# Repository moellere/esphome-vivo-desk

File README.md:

# ESPHome VIVO Desk

An [ESPHome](https://esphome.io/) external component that integrates a **VIVO
electric standing desk** (DESK‑V110EW class, with a **DC‑KS7** handset) into Home
Assistant — reading the live **height** and driving **up / down / memory presets**
— while the **physical handset keeps working normally** (display, buttons,
sustained holds, presets).

It works as a transparent serial **interposer**: a small ESP board is spliced
into the two‑wire link between the desk's handset and its controller ("brain").
The component relays the handset⇄brain traffic in both directions (so the handset
stays fully functional), parses the height telemetry for Home Assistant, and can
inject up/down/preset commands from HA alongside the live relay.

> ⚠️ **Use at your own risk.** This involves cutting into your desk's handset
> cable and driving the controller over a reverse‑engineered serial protocol.
> It is not affiliated with or endorsed by VIVO. You are responsible for your
> own hardware.

## Hardware

- **An ESP board with two UARTs.** **ESP32 is strongly recommended** — its
  hardware UARTs are full‑duplex, which is required to relay the fast
  bidirectional traffic while a button is held. ESP8266 (software serial) can
  *read* height and fire one‑shot presets, but its half‑duplex serial cannot
  sustain a held‑button relay reliably. An ESP32‑C3 (e.g. SuperMini) works well.
- The desk's handset cable carries two data lines (handset→brain and
  brain→handset) plus power/ground. You splice the ESP in the middle.

### Wiring

The desk bus is **3.3 V / 5 V TTL UART, 19200 8N1**. Cut the two data wires and
route them through two UARTs on the ESP (pick any free GPIOs; example shown):

| Desk line            | ESP pin (example) | UART        |
|----------------------|-------------------|-------------|
| Handset TX (output)  | GPIO4 (RX)        | `hand_uart` |
| Handset RX (input)   | GPIO5 (TX)        | `hand_uart` |
| Brain TX (output)    | GPIO6 (RX)        | `brain_uart`|
| Brain RX (input)     | GPIO7 (TX)        | `brain_uart`|
| Desk GND             | GND (see note)    | —           |

Identify the two **TX** (output) wires by metering them to GND with the desk
powered and idle — a UART line rests **high**. The other wire in each pair is the
matching RX.

> 💡 **Grounding tip.** If you power the ESP from a *separate* supply (e.g. USB)
> than the desk, tie the desk GND to the ESP GND through a **~100 Ω series
> resistor**. A direct hard ground can form a ground loop that prevents boot,
> while no ground at all leaves the reference floating and the Wi‑Fi radio can
> brown out under load. The resistor gives a defined reference without a hard
> loop. (If you power the ESP *from* the desk's 5 V line, a single shared ground
> is cleanest and no resistor is needed.) **The ESP32‑C3 is not 5 V‑tolerant — if
> your desk's data lines are 5 V, level‑shift them.**

## Usage

```yaml
external_components:
  - source: github://moellere/esphome-vivo-desk
    components: [ vivo_desk ]

uart:
  - id: hand_uart
    rx_pin: GPIO4   # <- Handset TX
    tx_pin: GPIO5   # -> Handset RX
    baud_rate: 19200
  - id: brain_uart
    rx_pin: GPIO6   # <- Brain TX
    tx_pin: GPIO7   # -> Brain RX
    baud_rate: 19200

vivo_desk:
  id: desk
  hand_uart: hand_uart
  brain_uart: brain_uart
  height:
    name: "Desk Height"
```

See [`example.yaml`](example.yaml) for a complete device config including
switches for Up/Down and buttons for the M1–M4 presets, plus the diagnostic
toggles (relay / emulate / sniff) used while bringing a new desk online.

### From a YAML lambda

```yaml
- lambda: id(desk).start_up();     # hold up (until stop())
- lambda: id(desk).start_down();   # hold down
- lambda: id(desk).stop();         # stop movement
- lambda: id(desk).goto_preset(1); # recall stored preset 1..4
```

## Modes

- **Relay** (default): forwards handset⇄brain in both directions so the physical
  handset works (display + buttons + holds + presets), parses height for HA, and
  injects HA up/down/preset commands alongside.
- **Emulate**: the ESP *is* the handset toward the brain — height + control
  without a physical handset present. Streams the handset heartbeat/version/acks.
- **Silent**: pure listen (sniffer) — transmits nothing, logs both lines. Useful
  for capturing a new desk's protocol.

## Protocol

The handset⇄brain protocol (ASCII frames, `:cmd data checksum;`, 19200 8N1) is
documented in [`docs/PROTOCOL.md`](docs/PROTOCOL.md), including the height frame
format, command frames, the heartbeat, and the checksum.

## License

[MIT](LICENSE).

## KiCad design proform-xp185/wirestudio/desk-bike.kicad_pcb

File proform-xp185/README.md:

# ProForm XP 185 U under-desk bike (ESPHome)

Turns a ProForm XP 185 U (Sears 831.21741.0 / ICON PFCCEX01210) into an
under-desk bike controlled by an ESP32 running ESPHome, with a small
OLED + rotary encoder module as the local UI and everything exposed to Home
Assistant.

**The original console and handlebars are left intact.** The only thing the
build touches is the 8-pin harness coming up from the base: unplug it from the
console, plug it into the new controller. Put the harness back and the bike is
stock again.

The bike has no lower control board and no serial bus: the console *is* the
controller. It drives a 6 V gearmotor that moves the magnetic brake, reads that
motor's feedback potentiometer, counts a crank reed switch, and amplifies the
grip pulse pads. `desk-bike.yaml` reproduces the first three from an ESP32 and
takes heart rate from a BLE chest strap instead of the grips.

> ⚠️ Not affiliated with ICON / ProForm. Check everything with a meter before
> applying power; you are responsible for your own hardware.

## Bill of materials

| Part | Notes |
|---|---|
| ESP32 dev board (`esp32dev`) | Classic ESP32 or S3. An ESP32‑C3 Super Mini works with the alternate pin map in the YAML but is tight on pins and RAM with BLE + Wi‑Fi. |
| 1.3" OLED + EC11 encoder module (Estardyn, SH1116 driver, I2C) | The same module as the scroller project: SDA, SCL, VCC, GND, encoder A/B, PSH, CON (KEY1), BAK (KEY0). |
| H‑bridge | **Recommended:** two MOSFET half‑bridges from IRF4905 + IRFZ44N + 2N3904 (below). Alternatives: a DRV8833/TB6612 module, or a dual 5 V relay board. |
| 5 V supply | USB‑C receptacle with **5.1 kΩ from CC1 and CC2 to GND**, 2 A or better. 470 µF + 100 nF at the bridge's motor rail, 100 nF across the motor. |
| Mating connector for the harness | Whatever the console used (an 8‑pin JST‑XH‑style header on the console PCB), or splice a pigtail. |
| BLE heart‑rate strap (optional) | Anything exposing the standard Heart Rate Service. |
| Resistors | 2 × 10 kΩ (GPIO pull‑downs on the bridge inputs), 2 × 470 Ω, 2 × 1 kΩ, 2 × 5.1 kΩ (USB‑C CC). |

## Circuit

### 8‑pin harness from the base (measured on this bike)

| Pin | Function | Goes to |
|---|---|---|
| 1 | Motor A | bridge output A |
| 2 | Motor B | bridge output B |
| 3 | Pot supply | **3V3** (not 5 V, so the wiper stays inside the ADC range) |
| 4 | Pot wiper | `pin_pot` (GPIO34) |
| 5 | Pot ground | GND |
| 6 | Chassis ground | GND (common with 5 and 8 on the console PCB) |
| 7 | Reed switch | `pin_reed` (GPIO27); internal pull‑up enabled |
| 8 | Reed switch return | GND |

Pins 1/2 reverse polarity across the motor to move the magnets toward or away
from the flywheel. The console's own bridge used one 2N4401 + 2N4403 per
side, so the motor's stall current is under 600 mA.

### ESP32 pin map (defaults in the YAML `substitutions:`)

| Signal | ESP pin | Notes |
|---|---|---|
| Bridge IN1 | GPIO18 | 10 kΩ pull‑down to GND so the motor can't run during boot |
| Bridge IN2 | GPIO19 | 10 kΩ pull‑down to GND |
| Pot wiper | GPIO34 | ADC1, input‑only pin |
| Reed switch | GPIO27 | other side to GND |
| OLED SDA / SCL | GPIO21 / GPIO22 | 3V3 and GND to the module |
| Encoder A / B | GPIO16 / GPIO17 | internal pull‑ups |
| Encoder push (PSH) | GPIO25 | internal pull‑up |
| Back (BAK / KEY0) | GPIO26 | internal pull‑up |
| Confirm (CON / KEY1) | GPIO33 | internal pull‑up |

### Recommended bridge: two MOSFET half‑bridges

(Editable SVG: `wirestudio/hbridge-schematic.svg`.)

Three parts per half‑bridge, no heat, nearly the full 5 V at the motor, and
the FET body diodes handle flyback. Build two, one per motor pin.

| Part | Pin | Connects to |
|---|---|---|
| IRF4905 (P‑MOSFET) | source | +5 V rail |
| IRF4905 | drain | MOTOR pin (harness 1 or 2) |
| IRF4905 | gate | node D |
| IRFZ44N (N‑MOSFET) | source | GND |
| IRFZ44N | drain | MOTOR pin |
| IRFZ44N | gate | node D |
| R1 470 Ω | | node D to +5 V |
| Q1 2N3904 (or 2N2222 / BC337) | collector | node D |
| Q1 | emitter | GND |
| Q1 | base | R2 1 kΩ to ESP GPIO (IN1 or IN2) |
| R3 10 kΩ | | ESP GPIO to GND |

GPIO **high** → Q1 on → node D ≈ 0 V → P‑FET on, N‑FET off → motor pin at
5 V. GPIO **low** → Q1 off → node D pulled to 5 V → P‑FET off, N‑FET on →
motor pin at GND. A floating GPIO at boot reads low through R3, so both pins
start grounded. TO‑220 pinout, flat face toward you, legs down, left→right:
**G‑D‑S**, tab = drain. 2N3904 flat face toward you: **E‑B‑C**. IRF9540
substitutes for the IRF4905. Do not use the 600 V FQPF parts on the low
side; their 3–5 V threshold is too high for a 5 V gate.

| IN1 | IN2 | Pin 1 | Pin 2 | Motor |
|---|---|---|---|---|
| low | low | GND | GND | off (dynamic brake) |
| high | low | +5 V | GND | direction A |
| low | high | GND | +5 V | direction B |
| high | high | +5 V | +5 V | off |

No combination passes current through a leg. The YAML still passes through
all‑off for one 50 ms tick before reversing.

### Alternative: dual relay board

Two SPDT relays: relay 1 COM → motor pin 1, relay 2 COM → motor pin 2, both
NO → +5 V, both NC → GND, VCC/JD‑VCC → 5 V, IN1/IN2 → the bridge GPIOs. Most
boards are active‑low: set `bridge_active_low: "true"`. If a relay clicks in
during boot, add 10 kΩ from that IN pin to 5 V.

### Power and grounding

One 5 V supply feeds everything. The ESP takes its 3.3 V from its own
regulator; the pot is fed from that 3.3 V. Make a single star ground at the
bridge/ESP; the harness grounds (5, 6, 8) and the chassis all land there.
Bring the motor rail in through the 470 µF + 100 nF pair at the bridge.

### Layout (perfboard)

Left to right, matching signal flow:

1. **USB‑C receptacle** with the two 5.1 kΩ CC resistors, feeding a 5 V rail
   along the top edge and GND along the bottom.
2. **Bridge** next to the harness connector: the two TO‑220 pairs side by
   side, their 2N3904 drivers and 470 Ω / 1 kΩ / 10 kΩ in front of them, the
   470 µF across the rails right there.
3. **Harness header** (8‑pin) on the edge: 1/2 to the bridge outputs, 3 to
   3V3, 4 to GPIO34, 5/6/8 to GND, 7 to GPIO27.
4. **ESP32** in the middle, GPIO side facing the bridge.
5. **OLED/encoder module** on a 4‑pin + 5‑pin header (or a short ribbon) so it
   can mount on the desk edge; keep the I2C leads under ~30 cm.

### WireStudio design

`wirestudio/design.json` models the whole controller for
[wirestudio](https://github.com/moellere/WireStudio): board, I2C bus, OLED,
encoder, three keys, pot ADC, reed input, and the MOSFET bridge as an
`hbridge_mosfet` component. That component and the library subcircuit
support it relies on shipped in WireStudio 0.3x
([WireStudio#262](https://github.com/moellere/WireStudio/pull/262)). The same
design is saved on the studio at wirestudio.dorktool.com as `desk-bike`.

| File | What it is |
|---|---|
| `wiring.txt` | pin map, passives, power budget; validates with no warnings in strict mode |
| `bom.csv` | every part with designators: Q1/Q4 IRF4905, Q2/Q5 IRFZ44N, Q3/Q6 2N3904, R1–R6, C1, C2, J1 motor terminal, J2 USB-C with R7/R8 and C3 |
| `desk-bike.skidl.py` | run with SKiDL to get `desk-bike.kicad_sch` |
| `cpl.csv` | JLCPCB pick-and-place positions |
| `desk-bike.kicad_pcb` | placed and autorouted board (Freerouting through wirestudio: 179 segments, 7 vias, every pad bound to its net) |
| `desk-bike-fab.zip` | JLCPCB upload bundle from the routed board: Gerbers, drill, BOM, CPL |

```
wirestudio-generate proform-xp185/wirestudio/design.json --strict \
  --out-ascii proform-xp185/wirestudio/wiring.txt
```

The USB-C input and its CC resistors are the `psu` instance of the
`usb_c_power_in` library part (WireStudio 0.39.0,
[#298](https://github.com/moellere/WireStudio/pull/298)): J2, R7/R8 5.1k, C3
10 µF, VBUS on the 5 V rail. The 8-pin harness connector needs passthrough connector
pins and a `net` connection target
([WireStudio#300](https://github.com/moellere/WireStudio/issues/300)); until
then add it in KiCad. The YAML wirestudio renders is a skeleton;
`desk-bike.yaml` is the real firmware (control loop, display pages, ride
tracking).

## Breadboard build (830-point)

(Editable SVG: `wirestudio/breadboard-layout.svg`; the wire list is printed on
the drawing.)

The ESP32‑DevKitC V4's pin rows are 1.0 in apart, so on a single 830‑point
board only **one** free tie point exists per pin, along one header. The
layout puts the module in rows **i** and **a** with the 3V3‑side header on
row i, so row **j** serves 5V, GND, 3V3, GPIO34, 27, 25, 26 and 33. The six
signals on the other header (GPIO16, 17, 18, 19, 21, 22) are reached by
seating a jumper in hole **e** of that column *before* pressing the module
in; it runs under the board and exits at the centre channel.

- Rails: + = 5 V, − = GND on both edges, joined at column 63; 5 V in from the
  USB‑C breakout at column 1. C1 470 µF (col 24) and C3 100 nF (col 53)
  across the bottom rail. A 3V3 mini‑bus is column 22 (rows f–j).
- Bridge on the bottom block: Q1/Q2/Q3 in columns 25–35, Q4/Q5/Q6 in
  40–50, standing TO‑220s with G‑D‑S in adjacent columns of row b, GPIO
  nodes at columns 36 and 51.
- RJ45 breakout in row j, columns 54–61 (pins 1–8, T568B colours); C2
  100 nF between the two motor pins (g57–g58).
- OLED/encoder cable on a 9‑pin header in row j, columns 25–33.

## Printed enclosure

See [`enclosure/`](enclosure/README.md): a parametric base + lid around the Perma‑Proto snap‑in tray, with a keystone port for the Cat‑6 harness extension, a USB‑C slot and the OLED/encoder module in the lid.

## The local UI

| Control | Action |
|---|---|
| Encoder turn | resistance level 1–8 (also `number.desk_bike_resistance_level` in HA) |
| Encoder push, short | next display page |
| Encoder push, hold 1–3 s | reset ride time and distance |
| Back | drop to level 1 (coast) and remember the previous level |
| Confirm | return to the remembered level |

Pages: **Ride** (level, rpm, ride clock, distance, time of day, heart rate),
**Goals** (odometer, next milestone, progress bar), **Heart rate** (large, plus strap status), **Brake** (pot voltage, target,
moving/idle, fault — the calibration page).

## Calibration

The brake is positioned by **burst‑and‑settle**: the motor runs for a short
burst, stops, waits 100 ms, and only then is the pot read (8‑sample average,
no motor current flowing, so no ground bounce and no coasting error). The
loop then decides the next burst, shorter as it gets close, and stops when
the settled reading is within `deadband_v` of the target. A move that
doesn't advance the wiper for `max_stalled_bursts` bursts, or runs past
`stall_timeout_ms`, raises **Brake Motor Fault**.

Levels map to wiper voltages through the eight‑entry `level_volts` table.
Magnetic drag rises steeply as the gap closes, so the useful tension lives in
the last part of the travel; a linear spread puts most levels where you feel
almost nothing. Measure the two ends, then bunch the levels toward the heavy
end:

1. Flash with the defaults and open the **Brake** page (or Home Assistant).
2. Press **Brake Jog IN1** a few times and watch the voltage. If it *rises*,
   leave `in1_raises_pot: "true"`; if it falls, set `"false"`.
3. Jog to the lightest position you want as level 1 and note the voltage, v1.
4. Jog the other way until the motor stalls at the heavy end, back off a few
   hundredths of a volt, note the voltage, v8. Pedal: this is level 8.
5. Fill `level_volts` with eight values from v1 to v8. A good start is
   `v1 + (v8 - v1) * sqrt((i - 1) / 7)` for i = 1..8, which is what the
   default table is for v1 = 0.40, v8 = 2.90. Then ride a few minutes at each
   level and move individual entries until the steps feel even.
6. Re‑flash.

If a level change ends in **Brake Motor Fault**, the Brake page shows the
settled position, the target and the burst count: a target outside the
measured range, the wrong `in1_raises_pot`, or a jam are the usual causes.
Change the level again to clear it.

## Distance, odometer and milestones

Distance is what a bike with a **27.5 in tire** would cover: 2.194 m per wheel
turn. A tire size alone doesn't give distance per pedal stroke, so there is
also a virtual `gear_ratio` (wheel turns per crank turn). The default 2.1 is
about a 34T x 16T gear: 4.61 m per stroke, 12 mph at 70 rpm. Change either
substitution to taste; `use_miles` switches the OLED and milestone text.

- **Ride Distance / Ride Time / Speed** are per session (hold the encoder to
  reset).
- **Odometer** is lifetime distance. The crank count behind it is stored in
  flash (written at most every 5 minutes) so it survives reboots and OTA
  updates. It is `total_increasing` with `device_class: distance`, which is
  what Home Assistant's utility meter needs.
  `desk_bike_package.yaml` is a ready package with daily, weekly, monthly
  and yearly meters. Copy it into `<config>/packages/` keeping an underscore
  name: HA uses the filename as the package slug and rejects hyphens.
- **Milestones** unlock on lifetime distance: Length of Manhattan, English
  Channel, Pontchartrain Causeway, a marathon, Panama Canal, Hadrian's Wall
  (117.5 km), a century ride, Katy Trail, Grand Canyon, Across Arkansas
  (I-40, 458 km), Natchez Trace, Pacific Coast Highway, Land's End to John
  o'Groats, a Tour de France, Appalachian Trail, Route 66, New York to LA,
  the Ming Great Wall, and around the Earth. The list is one table in the
  YAML; keep it sorted if you add your own.
  Each unlock publishes **Last Milestone**, shows a 15 s banner on the OLED,
  and fires the HA event `esphome.desk_bike_milestone` (`title`,
  `odometer_km`) for automations. **Next Milestone** and **Milestone
  Progress** show what's coming; the OLED's *Goals* page has the same with a
  progress bar.

## Heart rate

Set `hrm_mac`. On boot with the strap on, the ESPHome log lists nearby BLE
devices with their MACs. The **Heart rate** page shows whether the strap is
connected. (The grip electrodes on the handlebars are not used; they need
both hands on the bars, which doesn't fit desk use. An AD8232 version lives
in this repo's history if you ever want it.)

## Entities

| Entity | Type | Purpose |
|---|---|---|
| Resistance Level | number 1–8 | Sets the brake |
| Cadence, Crank Revolutions | sensor | From the reed switch |
| Ride Time, Ride Distance, Speed | sensor | Session counters; Reset Ride button clears them |
| Odometer | sensor | Lifetime distance, kept in flash; source for HA utility meters |
| Last Milestone, Next Milestone, Milestone Progress | text / sensor | Distance achievements |
| Pedaling | binary | Cadence > 0 |
| Heart Rate | sensor | From the BLE strap |
| Button, Back, Confirm | binary | The module's keys, for your own automations |
| Brake Position, Brake Moving, Brake Motor Fault | diagnostics | Loop state |
| Brake Jog IN1 / IN2 / Stop | buttons | Calibration and manual override |

## Config layout

`desk-bike.yaml` follows the same shape as the scroller project: `common/
base.yaml` and `common/sensor.yaml` are merged in, fonts come from
`common/fonts/` (slkscr, BebasNeue‑Regular, arial). Remember that a
`base.yaml` brings wifi/api/ota/logger in through `packages:`, which
deep‑merge, so the `wifi:` block here only adds `fast_connect` and
`power_save_mode: none`. Keys merged with `<<:` do not deep‑merge, so this
file's `sensor:` list replaces `sensor.yaml`'s; uptime and Wi‑Fi signal are
repeated in it.

## Not included (yet)

- **Bluetooth FTMS** so Zwift or similar can read cadence and set resistance.
  ESPHome's `esp32_ble_server` can host the service, but the ESP would then be
  a BLE central (strap) and peripheral (FTMS) at once, so budget memory.
- A power estimate. The console's watts were a lookup of level × cadence; do
  the same in a template sensor once you have numbers you trust.

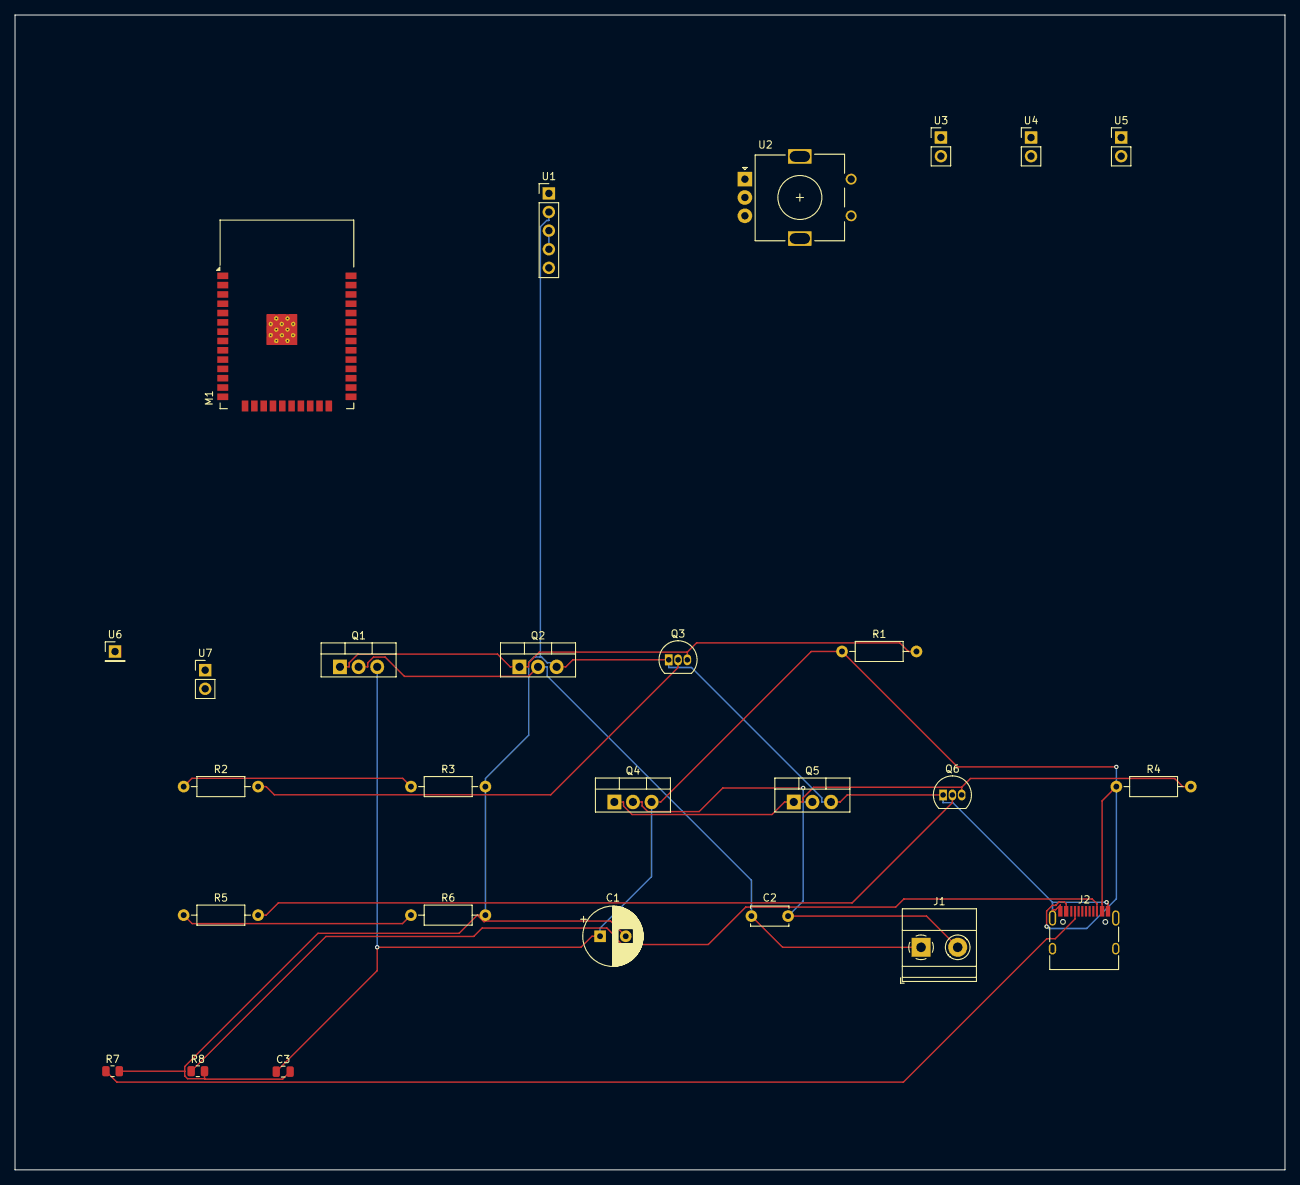
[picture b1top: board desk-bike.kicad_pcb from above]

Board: 2 copper layers, 173.3 x 157.6 mm, 27 parts (0 on the bottom side), 13 nets.

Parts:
C1: 470uF; CP_Radial_D8.0mm_P3.50mm
C2: 100nF; C_Disc_D5.0mm_W2.5mm_P5.00mm
C3: 10uF; C_0805_2012Metric
J1: Motor; TerminalBlock_Phoenix_MKDS-1,5-2_1x02_P5.00mm_Horizontal
J2: USB-C; USB_C_Receptacle_HRO_TYPE-C-31-M-12
M1: esp32-devkitc-v4; ESP32-WROOM-32
Q1, Q4: IRF4905; TO-220-3_Vertical
Q2, Q5: IRFZ44N; TO-220-3_Vertical
Q3, Q6: 2N3904; TO-92_Inline
R1, R4: 470; R_Axial_DIN0207_L6.3mm_D2.5mm_P10.16mm_Horizontal
R2, R5: 1k; R_Axial_DIN0207_L6.3mm_D2.5mm_P10.16mm_Horizontal
R3, R6: 10k; R_Axial_DIN0207_L6.3mm_D2.5mm_P10.16mm_Horizontal
R7, R8: 5.1k; R_0805_2012Metric
U1: SSD1306; PinHeader_1x05_P2.54mm_Vertical
U2: Rotary encoder; RotaryEncoder_Alps_EC11E_Vertical_H20mm
U3, U4, U5: Input; PinHeader_1x02_P2.54mm_Vertical
U6: ADC sense; PinHeader_1x01_P2.54mm_Vertical
U7: Pulse source; PinHeader_1x02_P2.54mm_Vertical

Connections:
+5V: C1.1, C3.1, J2.A4, J2.A9, J2.B4, J2.B9, Q1.3, Q4.3, R1.1, R4.1
BUS_i2c0: U1.3, U1.4
GND: C1.2, C3.2, J2.A1, J2.A12, J2.B1, J2.B12, J2.S1, Q2.3, Q3.1, Q5.3, Q6.1, R3.2, R6.2, R7.2, R8.2, U1.2
GPIO_GPIO18: R2.1, R3.1
GPIO_GPIO19: R5.1, R6.1
bridge_base_a: Q3.2, R2.2
bridge_base_b: Q6.2, R5.2
bridge_gate_a: Q1.1, Q2.1, Q3.3, R1.2
bridge_gate_b: Q4.1, Q5.1, Q6.3, R4.2
bridge_out_a: C2.1, J1.1, Q1.2, Q2.2
bridge_out_b: C2.2, J1.2, Q4.2, Q5.2
psu_cc1: J2.A5, R7.1
psu_cc2: J2.B5, R8.1

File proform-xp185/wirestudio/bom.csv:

Comment,Designator,Footprint,JLCPCB Part #
100nF,C2,Capacitor_THT:C_Disc_D5.0mm_W2.5mm_P5.00mm,
10k,"R3,R6",Resistor_THT:R_Axial_DIN0207_L6.3mm_D2.5mm_P10.16mm_Horizontal,
10uF,C3,Capacitor_SMD:C_0805_2012Metric,
1k,"R2,R5",Resistor_THT:R_Axial_DIN0207_L6.3mm_D2.5mm_P10.16mm_Horizontal,
2N3904,"Q3,Q6",Package_TO_SOT_THT:TO-92_Inline,
470,"R1,R4",Resistor_THT:R_Axial_DIN0207_L6.3mm_D2.5mm_P10.16mm_Horizontal,
470uF,C1,Capacitor_THT:CP_Radial_D8.0mm_P3.50mm,
5.1k,"R7,R8",Resistor_SMD:R_0805_2012Metric,
ADC sense,U6,Connector_PinHeader_2.54mm:PinHeader_1x01_P2.54mm_Vertical,
ESP32-DevKitC-V4,M1,RF_Module:ESP32-WROOM-32,
IRF4905,"Q1,Q4",Package_TO_SOT_THT:TO-220-3_Vertical,
IRFZ44N,"Q2,Q5",Package_TO_SOT_THT:TO-220-3_Vertical,
Input,"U3,U4,U5",Connector_PinHeader_2.54mm:PinHeader_1x02_P2.54mm_Vertical,
Motor,J1,"TerminalBlock_Phoenix:TerminalBlock_Phoenix_MKDS-1,5-2_1x02_P5.00mm_Horizontal",
Pulse source,U7,Connector_PinHeader_2.54mm:PinHeader_1x02_P2.54mm_Vertical,
Rotary encoder,U2,Rotary_Encoder:RotaryEncoder_Alps_EC11E_Vertical_H20mm,
SSD1306,U1,Connector_PinHeader_2.54mm:PinHeader_1x05_P2.54mm_Vertical,
USB-C,J2,Connector_USB:USB_C_Receptacle_HRO_TYPE-C-31-M-12,
